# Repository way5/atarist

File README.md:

# <p align="center">Atarist</p>

<h2>Table of Contents</h2>

+ [**- Touch Tablet CX-77**](#--touch-tablet-cx-77)
+ [**- SIO Plug**](#--sio-plug)

<br>

## **- [Touch Tablet CX-77](./models/touchtablet_cx_77/)**

<table cellpadding="0" cellspacing="0" width="100%">
<tr><td width="160px">

</td><td>
The ATARI Touch Tablet is an art and graphics controller designed for use with all ATARI Home Computers. You can quickly and easily create your own computer art and graphics-without writing complex programs using the AtariArtist™ software included with the Touch Tablet.
<p>For those folks who don't have the wired-pen (stylus) of the Tablet, the following models can help to reproduce this part.</p>
</td></tr></table>

<br>

>**A WORD OF APPRECIATION:**\
Special thanks to [**John Cove**](https://www.facebook.com/groups/ataristsales) who kindly provided the required data. There are more cool stuffs for retroware on his web-page [www.ataristsales.co.uk](https://www.ataristsales.co.uk).

<br>

**BOM:**

- Cable (2 wire) - 1pcs
- Audio jack (2.5mm) - 1pcs.
- PCB (see attached schematics):
  - SMD pushbutton switch - 1pcs (height ~1.6mm), see below.
  - 1k SMD resistor - 1pcs.

<br>

|  |  |
|:----:|:----:|

**NOTE:** \
The debouncing circuit is not required.<br>

---

**<h3>+ Photos</h3>**

|  |  |  |  |  |  |  |
|:---:|:---:|:---:|:---:|:---:|:---:|:---:|

</br>

## **- [SIO Plug](./models/sio_plug/)**

<table cellpadding="0" cellspacing="0" width="100%">
<tr><td width="160px">

</td><td>
The Serial Input/Output system was a proprietary peripheral bus and related software protocol stacks used on the Atari 8-bit computers to provide most input/output duties for those computers.
Printable 3D model of the most common version of MOLEX SIO plug you can download from <a href="/models/sio_plug/">here</a>.
</td></tr></table>

<br>

**BOM:**

- Bolt + Nut (M3) - 1pcs.

----

**<h3>+ Photos</h3>**

|  |  |  |
|:---:|:---:|:---:|

<br><hr>

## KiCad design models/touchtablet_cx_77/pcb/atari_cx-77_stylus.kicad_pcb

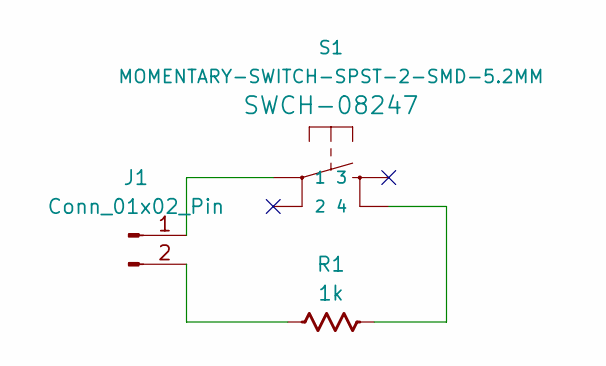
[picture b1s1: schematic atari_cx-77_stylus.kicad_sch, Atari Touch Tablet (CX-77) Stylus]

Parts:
J1: Conn_01x02_Pin; SolderWire-1sqmm_1x02_P5.4mm_D1.4mm_OD2.7mm
R1: 1k; R_1206_3216Metric_Pad1.42x1.75mm_HandSolder
S1: MOMENTARY-SWITCH-SPST-2-SMD-5.2MM; TACTILE_SWITCH_SMD_5.2MM

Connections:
unnamed: J1.1, S1.1
unnamed: J1.2, R1.2
unnamed: R1.1, S1.4

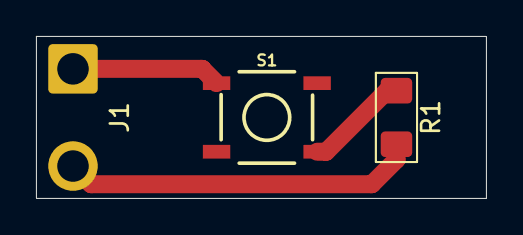
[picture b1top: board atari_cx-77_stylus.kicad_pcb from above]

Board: 2 copper layers, 25.0 x 9.0 mm, 3 parts (0 on the bottom side), 3 nets.

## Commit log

2024-05-11 readme upd.
